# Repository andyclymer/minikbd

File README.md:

# MiniKbd

The MiniKbd is a USB device based on the [Adafruit Trinket M0](https://learn.adafruit.com/adafruit-trinket-m0-circuitpython-arduino) development board which is programmable with CircuitPython. The parts are [available for sale on Tindie](https://www.tindie.com/products/andyclymer/minikbd-little-diy-mechanical-keyboard-kit/), with build documentation and software samples available in this repo.

The MiniKbd is programmable with CircuitPython, each key can be easily customized to perform any combination of keystroke or mouse movement. When plugging it in over USB, your computer will recognize it as a “USB HID” (Human Interface Device), as if a keyboard or mouse had been plugged in. The keystrokes that are output by the MiniKbd can then be configured by editing the CircuitPython code running on the device.

The project came out of the idea of wanting a keyboard that simply had a larger set of arrow keys that I could position to the left side of my keyboard. [OSH Park](http://www.oshpark.com), the prototyping service that I use  to manufacture PCBs will always make boards in sets of three, so instead of having three of the same device I designed the MiniKbd to be built in three separate ways —

# Documentation and parts list

The MiniKbd is a DIY project, and I hope that you'll build one! Complete build documentation, parts list, and KiCad source files can be found in the [Hardware](./Hardware) directory of this repo, and code examples can be found inthe [Software](./Software) directory.

## Buying it
[The MiniKbd kit is available for sale on Tindie](https://www.tindie.com/products/andyclymer/minikbd-little-diy-mechanical-keyboard-kit/) if you'd like to build one (or two) for yourself!

# Build the MiniKbd in one of three layouts

[The build documentation can be found in the Hardware directory of this repo.](./Hardware)

### Layout #1: “Six Keyboard Keyswitches”

Six keyboard keys, with component footprints for the most popular Cherry MX, Cherry ML and Kalih Low Profile keyswitches. Choose keyswitches that are as clicky and springy as you wish.

Since the Trinket M0 only has five general purpose IO pins and this variation has six keyswitches, they are wired up as a matrix of three rows by two columns of keyswitches. I've written a simple library to read the keypresses of a small [button matrix](https://github.com/andyclymer/circuitpython_libs/tree/master/buttonMatrix) like this one.

### Layout #2: “Two Rotary Encoders”

Whereas a “potentiometer” is the kind of knob designed to turn from 0 to 100% (like a volumne knob), its cousin the Rotary Encoder can freely turn continuously in either direction, clicking like a jog-dial as it turns (usually 12 or 24 clicks per rotation). With each click, the MiniKbd receives a signal that it's able to interpret to know whether it was turned clockwise or counterclockwise. Then, with each click, a keyboard command can be sent to the computer.

For instance, if the "z" and "x" keys are set up to zoom in and out in your drawing application, you can make one of the encoders into a zoom knob by having it type the letter "z" with each click in one direction, and the letter "x" in the other. 

### Layout #3: “One rotary encoder and two keyboard keyswitches”

The best of both worlds, almost like a little mouse that only has a scroll wheel and two buttons for clicking.

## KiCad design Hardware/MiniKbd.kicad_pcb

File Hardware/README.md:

# MiniKbd Hardware

The MiniKbd is designed to be built in one of three configurations:

- “Six keyboard keyswitches”
- “Two rotary encoders”
- “One rotary encoder and two keyboard keyswitches”

## Buying it
[The MiniKbd kit is available for sale on Tindie](https://www.tindie.com/products/andyclymer/minikbd-little-diy-mechanical-keyboard-kit/) if you'd like to build one (or two) for yourself! I'm selling the PCB, four sticker feet, and an optional set of hardware for use with the enclosure. The remaining parts will need to be sourced separately, but they can be found fairly easily from my guide below.

## Parts List
The full list of parts for each of the three configurations along with a buying guide can be found in the [Parts List](./PartsList.md) file in this directory.

## Building it
Build guides are available for all three configurations:
- [Build Doc — Six Keyboard Keyswitches](./Build-SixKeyswitches.md)
- [Build Doc — Two Rotary Encoders](./Build-TwoEncoders.md)
- [Build Doc — One Rotary Encoder and Two Keyboard Keyswitches](./Build-OneEncoderTwoSwitches.md)

## MiniKbd Enclosure
A very simple laser cut enclosure can be made with the plans in the [Enclosure](./Enclosure) directory. Files are available to send for laser cutting at Ponoko if you don't have access to your own laser cutter.

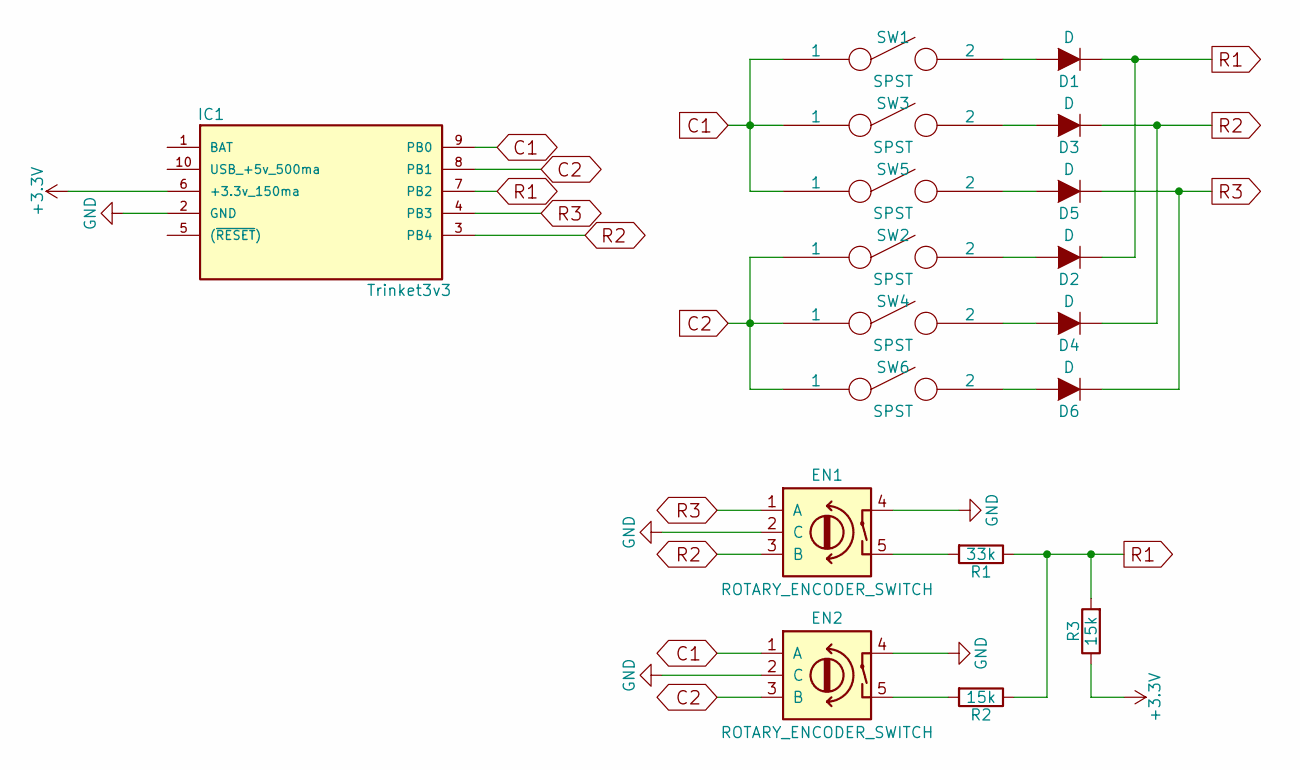
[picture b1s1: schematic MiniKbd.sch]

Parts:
D1, D2, D3, D4, D5, D6: D; Diode_SmallDualSize
EN1, EN2: ROTARY_ENCODER_SWITCH; Encoder_Bourns_PEC11_12mm_123
IC1: Trinket3v3; Trinket_3v3
R1: 33k; R_Axial_DIN0204_L3.6mm_D1.6mm_P7.62mm_Horizontal
R2, R3: 15k; R_Axial_DIN0204_L3.6mm_D1.6mm_P7.62mm_Horizontal
SW1, SW2, SW3, SW4, SW5, SW6: SPST; CHERRY_MXML_KAILH_PCB_100H

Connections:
+3V3: IC1.6 (+3.3v_150ma), R3.1
C1: EN2.1 (A), IC1.9 (PB0), SW1.1, SW3.1, SW5.1
C2: EN2.3 (B), IC1.8 (PB1), SW2.1, SW4.1, SW6.1
GND: EN1.2 (C), EN1.4, EN2.2 (C), EN2.4, IC1.2 (GND)
unnamed: D1.2 (A), SW1.2
unnamed: D2.2 (A), SW2.2
unnamed: D3.2 (A), SW3.2
unnamed: D4.2 (A), SW4.2
unnamed: D5.2 (A), SW5.2
unnamed: D6.2 (A), SW6.2
unnamed: EN1.5, R1.2
unnamed: EN2.5, R2.2
R1: D1.1 (K), D2.1 (K), IC1.7 (PB2), R1.1, R2.1, R3.2
R2: D3.1 (K), D4.1 (K), EN1.3 (B), IC1.3 (PB4)
R3: D5.1 (K), D6.1 (K), EN1.1 (A), IC1.4 (PB3)

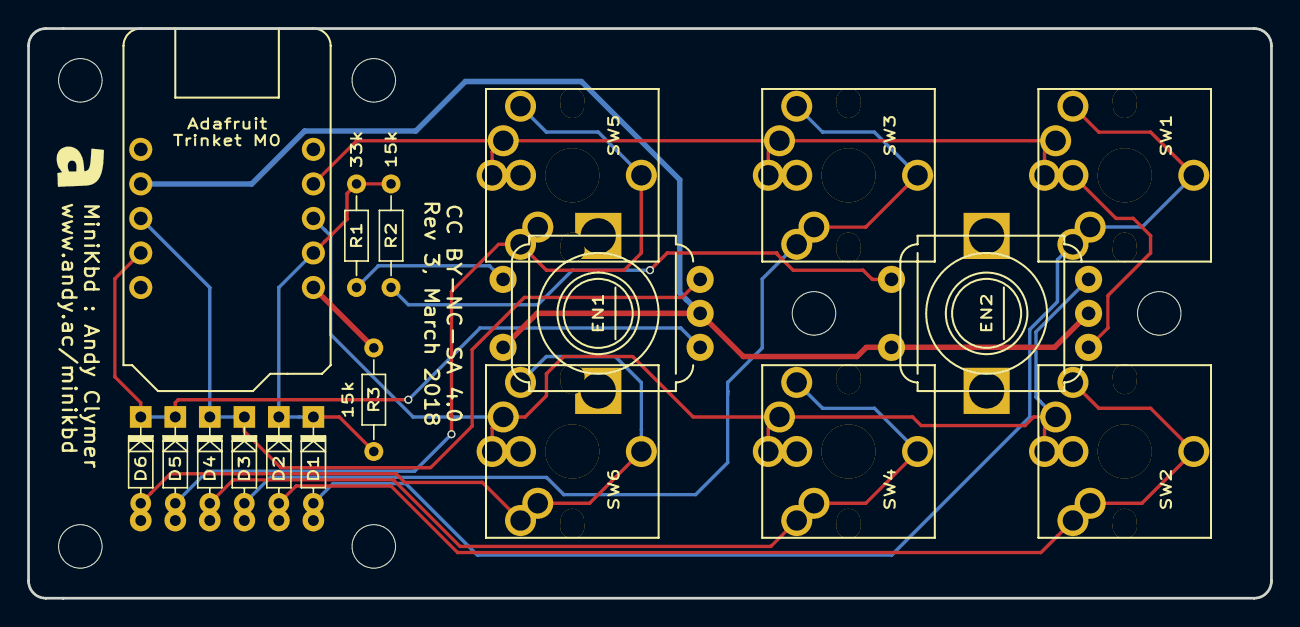
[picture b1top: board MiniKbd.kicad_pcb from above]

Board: 2 copper layers, 91.4 x 41.9 mm, 18 parts (0 on the bottom side), 15 nets.

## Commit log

2018-03-31 Updated .gitignore to include Python and KiCad files
2018-03-31 First commit of the hardware and general repo layout
2018-04-01 Adding enclosure laser files
2018-04-01 Adding another image
2018-04-02 Adding more photos
2018-04-05 Updated the enclosure art
2018-04-05 Moving files to the KiCad Project folder
2018-04-05 ...moving the readme file back to the Hardware folder
2018-04-05 Added schematic PDF
2018-04-05 Folder rename
2018-04-24 Adding enclosure build images
2018-08-06 Adding build images
2018-08-07 Adding more enclosure images
2018-08-13 New photo
2018-08-18 Adds an untested key stabalizer to the laser enclosure PDF
2018-10-11 Adding sample code
2018-10-19 Adding sample code for the encoder with two keys
2018-10-19 Replaced spaces with tabs for consistency
2018-10-24 Making some new sample code, and renaming some others
2018-10-29 First pass at a simplified keyboard matrix library
2018-10-30 Finishing up work on the simplified button matrix code
2018-11-17 Changing a pin name from A1 to D2 for compatibility with older versions of CircuitPython
2018-11-27 Fixing pin numbers in the TwoEncoder-Volume example
2018-11-27 Updating the pin numbers in the TwoEncoder-Keyboard example
2018-11-27 Fixing pin numbers
2018-11-29 Adding more build photos
2018-11-29 Renaming some build images
2018-11-29 Adding smaller build images
2018-11-29 More build photos
2018-11-30 Adding a delay for the encoder button pressing
2018-11-30 Adding an example with the encoders to have more than one mode
2018-11-30 Adding a readme
2018-12-02 Fixing a typo
2019-08-21 Updating two of the ponoko laser files to fix upload problems to ponoko.com
2020-03-18 fix for new adafruit_hid library in the sixkey main.py
2020-03-21 fix for new adafruit_hid library in the other main.py files

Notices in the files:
Hardware/KiCad Project/MiniKbd.sch:
CC BY-NC-SA 4.0
